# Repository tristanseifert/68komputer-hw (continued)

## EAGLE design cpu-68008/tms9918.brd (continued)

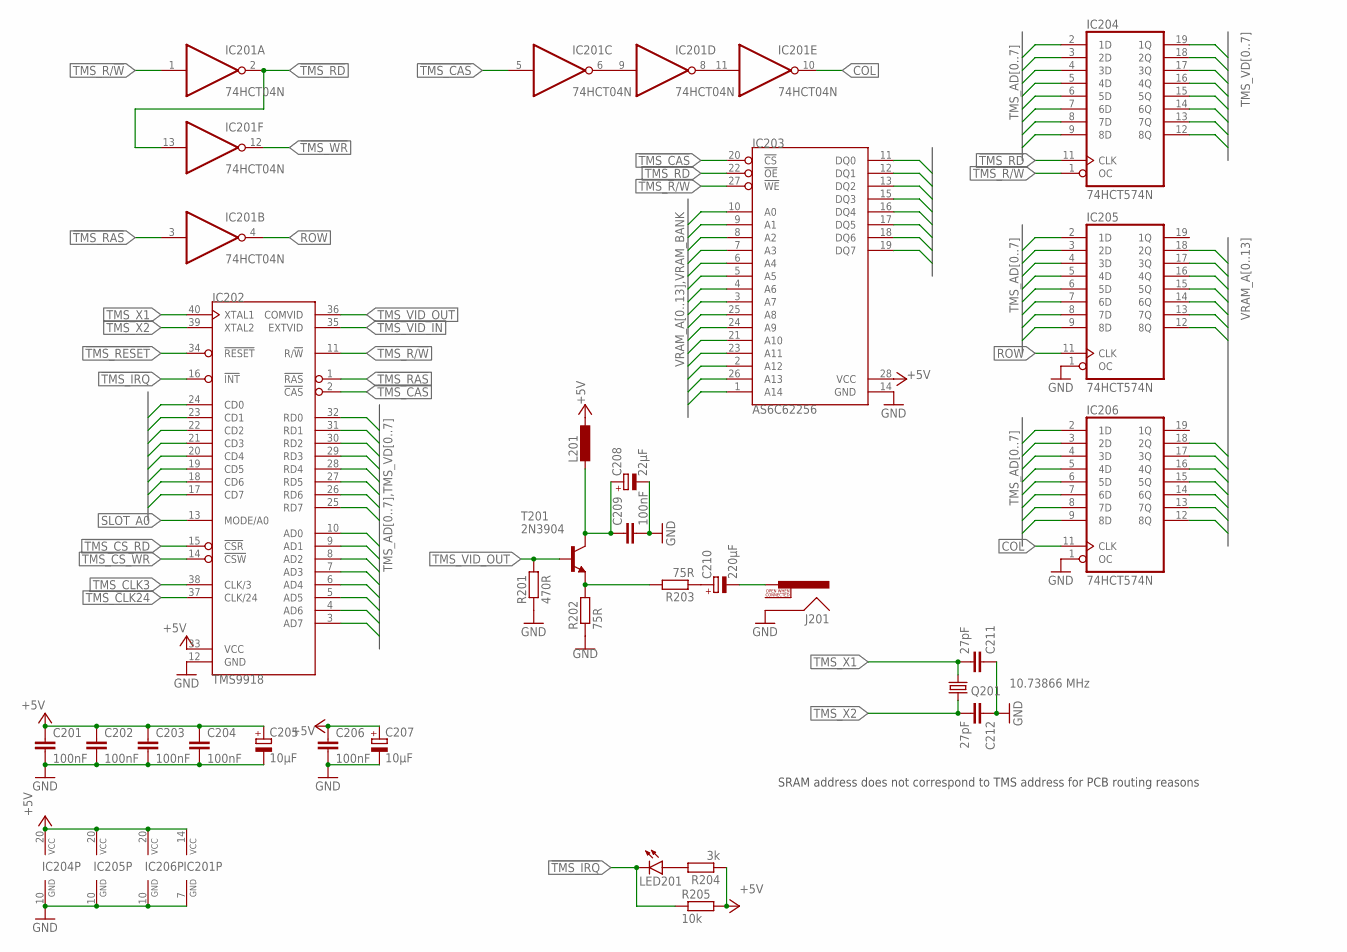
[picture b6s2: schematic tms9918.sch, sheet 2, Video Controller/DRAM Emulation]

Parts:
C201, C202, C203, C204, C206, C209: 100nF; C0805; MOUSER 710-885012207072
C205, C207: 10µF; SMC_B; MOUSER 581-TAJB106K020RNJV
C208: 22µF; E2-5; MOUSER 710-860010372002
C210: 220µF; E2,5-7; MOUSER 710-860020373010
C211, C212: 27pF; C0805; MOUSER 80-C0805C270K5HACTU
IC201: 74HCT04N; DIL14; MOUSER 595-SN74HCT04N
IC202: TMS9918; DIL40
IC203: AS6C62256; DIL28-6; MOUSER_SOCKET 575-1104762841001000
IC204, IC205, IC206: 74HCT574N; DIL20; MOUSER 595-SN74HCT574N
J201: RCALOCK; RCA_LOCK; MOUSER 502-PJRAN1X1U04AU
L201: L-EUL2012C; L2012C; MOUSER 963-BK2125HS101-T
LED201: LEDCHIPLED_1206; CHIPLED_1206; MOUSER 710-156120VS75300
Q201: 10.73866 MHz; HC49/S; MOUSER 449-LFXTAL029962REEL
R201: 470R; R2012; MOUSER 652-CR0805FX-4700ELF
R202, R203: 75R; R2012; MOUSER 652-CR0805FX-75R0ELF
R204: 3k; R2012; MOUSER 652-CR0805JW-302ELF
R205: 10k; R2012; MOUSER 652-CR0805FX-1002ELF
T201: 2N3904; TO92; MOUSER 512-2N3904BU

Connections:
!TMS_CAS: IC201.5 (I), IC202.2 (!CAS), IC203.20 (!CS)
!TMS_CS_RD: IC202.15 (!CSR); also elsewhere on the board
!TMS_CS_WR: IC202.14 (!CSW); also elsewhere on the board
!TMS_IRQ: IC202.16 (!INT), LED201.C, R205.1; also elsewhere on the board
!TMS_RAS: IC201.3 (I), IC202.1 (!RAS)
!TMS_RD: IC201.2 (O), IC201.13 (I), IC203.22 (!OE), IC204.11 (CLK)
!TMS_RESET: IC202.34 (!RESET); also elsewhere on the board
!TMS_WR: IC201.12 (O)
+5V: C201.1, C202.1, C203.1, C204.1, C205.+, C206.1, C207.+, IC201.14 (VCC), IC202.33 (VCC), IC203.28 (VCC), IC204.20 (VCC), IC205.20 (VCC), IC206.20 (VCC), L201.1, R204.1, R205.2; also elsewhere on the board
COL: IC201.10 (O), IC206.11 (CLK)
GND: C201.2, C202.2, C203.2, C204.2, C205.-, C206.2, C207.-, C208.-, C209.2, C211.1, C212.1, IC201.7 (GND), IC202.12 (GND), IC203.14 (GND), IC204.10 (GND), IC205.1 (OC), IC205.10 (GND), IC206.1 (OC), IC206.10 (GND), J201.SHELL, R201.1, R202.1; also elsewhere on the board
unnamed: IC201.8 (O), IC201.11 (I)
unnamed: IC201.6 (O), IC201.9 (I)
unnamed: C208.+, C209.1, L201.2, T201.1 (C)
unnamed: R202.2, R203.2, T201.3 (E)
unnamed: C210.+, R203.1
unnamed: C210.-, J201.PIN
unnamed: LED201.A, R204.2
ROW: IC201.4 (O), IC205.11 (CLK)
SLOT_A0: IC202.13 (MODE/A0); also elsewhere on the board
SLOT_D0: IC202.17 (CD7); also elsewhere on the board
SLOT_D1: IC202.18 (CD6); also elsewhere on the board
SLOT_D2: IC202.19 (CD5); also elsewhere on the board
SLOT_D3: IC202.20 (CD4); also elsewhere on the board
SLOT_D4: IC202.21 (CD3); also elsewhere on the board
SLOT_D5: IC202.22 (CD2); also elsewhere on the board
SLOT_D6: IC202.23 (CD1); also elsewhere on the board
SLOT_D7: IC202.24 (CD0); also elsewhere on the board
TMS_AD0: IC202.10 (AD0), IC204.2 (1D), IC205.9 (8D), IC206.9 (8D)
TMS_AD1: IC202.9 (AD1), IC204.3 (2D), IC205.8 (7D), IC206.8 (7D)
TMS_AD2: IC202.8 (AD2), IC204.4 (3D), IC205.7 (6D), IC206.7 (6D)
TMS_AD3: IC202.7 (AD3), IC204.5 (4D), IC205.6 (5D), IC206.6 (5D)
TMS_AD4: IC202.6 (AD4), IC204.6 (5D), IC205.5 (4D), IC206.5 (4D)
TMS_AD5: IC202.5 (AD5), IC204.7 (6D), IC205.4 (3D), IC206.4 (3D)
TMS_AD6: IC202.4 (AD6), IC204.8 (7D), IC205.3 (2D), IC206.3 (2D)
TMS_AD7: IC202.3 (AD7), IC204.9 (8D), IC205.2 (1D), IC206.2 (1D)
TMS_CLK3: IC202.38 (CLK/3); also elsewhere on the board
TMS_CLK24: IC202.37 (CLK/24)
TMS_R/!W!: IC201.1 (I), IC202.11 (R/!W!), IC203.27 (!WE), IC204.1 (OC)
TMS_VD0: IC202.32 (RD0), IC203.11 (DQ0), IC204.19 (1Q)
TMS_VD1: IC202.31 (RD1), IC203.12 (DQ1), IC204.18 (2Q)
TMS_VD2: IC202.30 (RD2), IC203.13 (DQ2), IC204.17 (3Q)
TMS_VD3: IC202.29 (RD3), IC203.15 (DQ3), IC204.16 (4Q)
TMS_VD4: IC202.28 (RD4), IC203.16 (DQ4), IC204.15 (5Q)
TMS_VD5: IC202.27 (RD5), IC203.17 (DQ5), IC204.14 (6Q)
TMS_VD6: IC202.26 (RD6), IC203.18 (DQ6), IC204.13 (7Q)
TMS_VD7: IC202.25 (RD7), IC203.19 (DQ7), IC204.12 (8Q)
TMS_VID_IN: IC202.35 (EXTVID)
TMS_VID_OUT: IC202.36 (COMVID), R201.2, T201.2 (B)
TMS_X1: C211.2, IC202.40 (XTAL1), Q201.1
TMS_X2: C212.2, IC202.39 (XTAL2), Q201.2
VRAM_A0: IC203.10 (A0), IC205.12 (8Q)
VRAM_A1: IC203.9 (A1), IC205.13 (7Q)
VRAM_A2: IC203.8 (A2), IC205.14 (6Q)
VRAM_A3: IC203.7 (A3), IC205.15 (5Q)
VRAM_A4: IC203.6 (A4), IC205.16 (4Q)
VRAM_A5: IC203.5 (A5), IC205.17 (3Q)
VRAM_A6: IC203.4 (A6), IC205.18 (2Q)
VRAM_A7: IC203.3 (A7), IC206.17 (3Q)
VRAM_A8: IC203.25 (A8), IC206.15 (5Q)
VRAM_A9: IC203.24 (A9), IC206.14 (6Q)
VRAM_A10: IC203.21 (A10), IC206.12 (8Q)
VRAM_A11: IC203.23 (A11), IC206.13 (7Q)
VRAM_A12: IC203.2 (A12), IC206.18 (2Q)
VRAM_A13: IC203.26 (A13), IC206.16 (4Q)
VRAM_BANK: IC203.1 (A14); also elsewhere on the board

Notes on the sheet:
SRAM address does not correspond to TMS address for PCB routing reasons

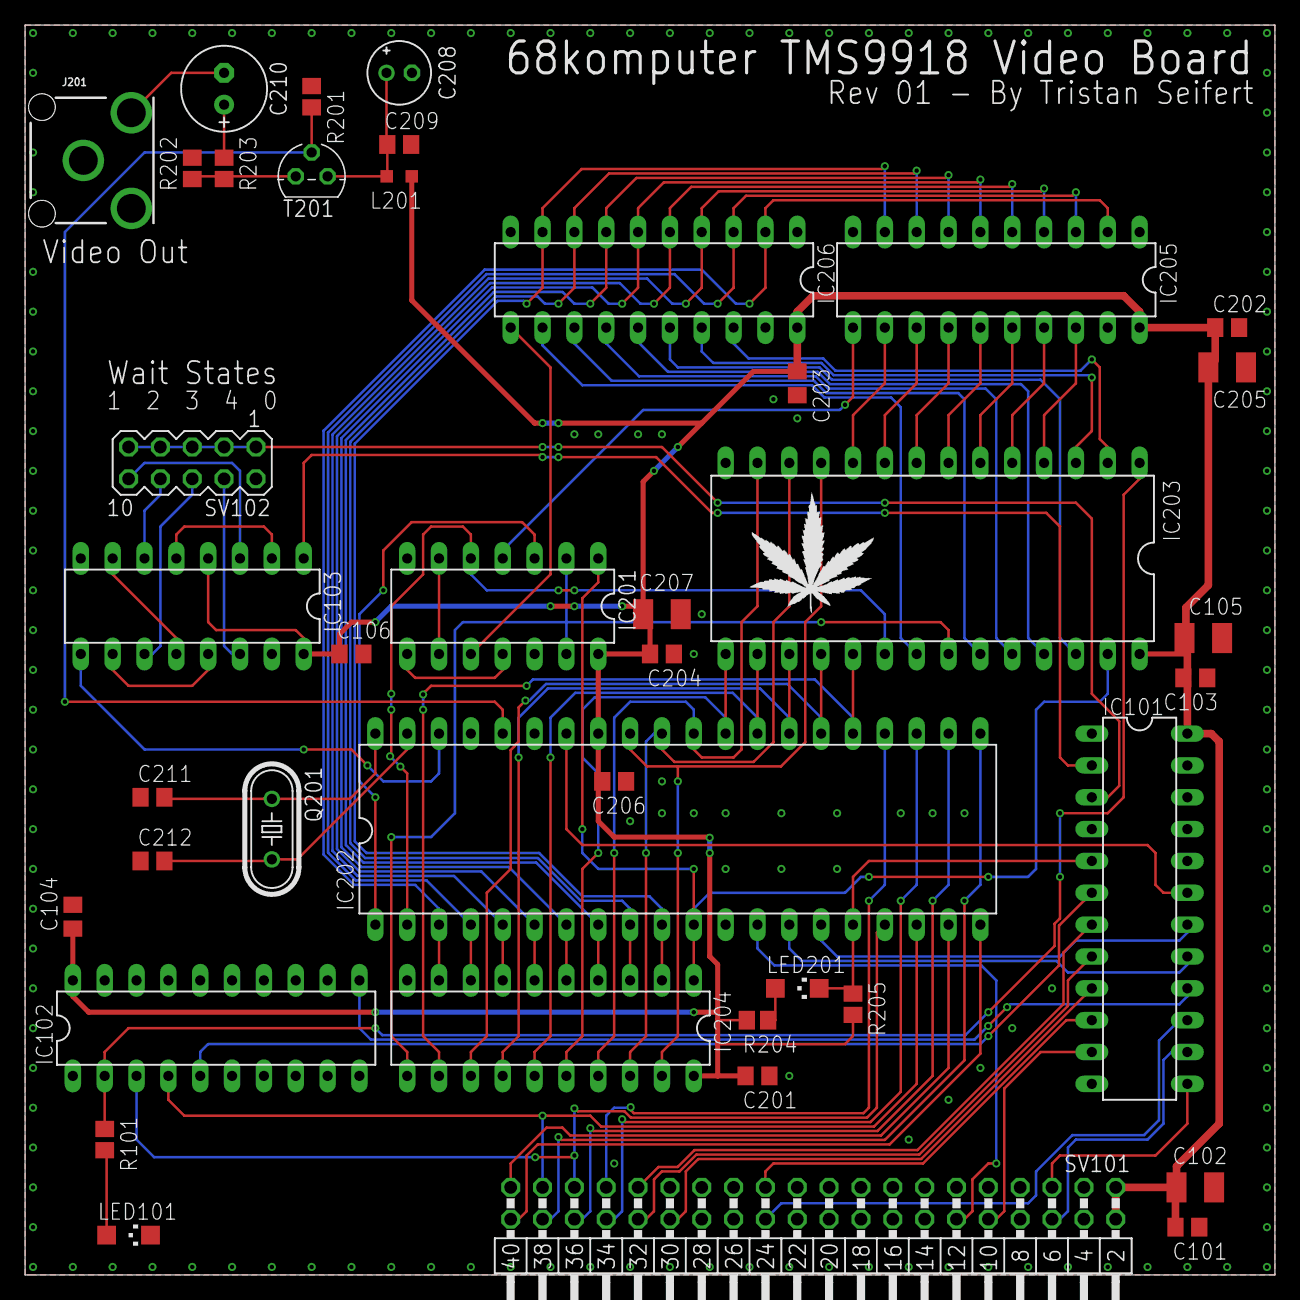
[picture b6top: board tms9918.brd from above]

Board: 2 copper layers, 99.7 x 99.7 mm, 42 parts (0 on the bottom side), 83 nets.

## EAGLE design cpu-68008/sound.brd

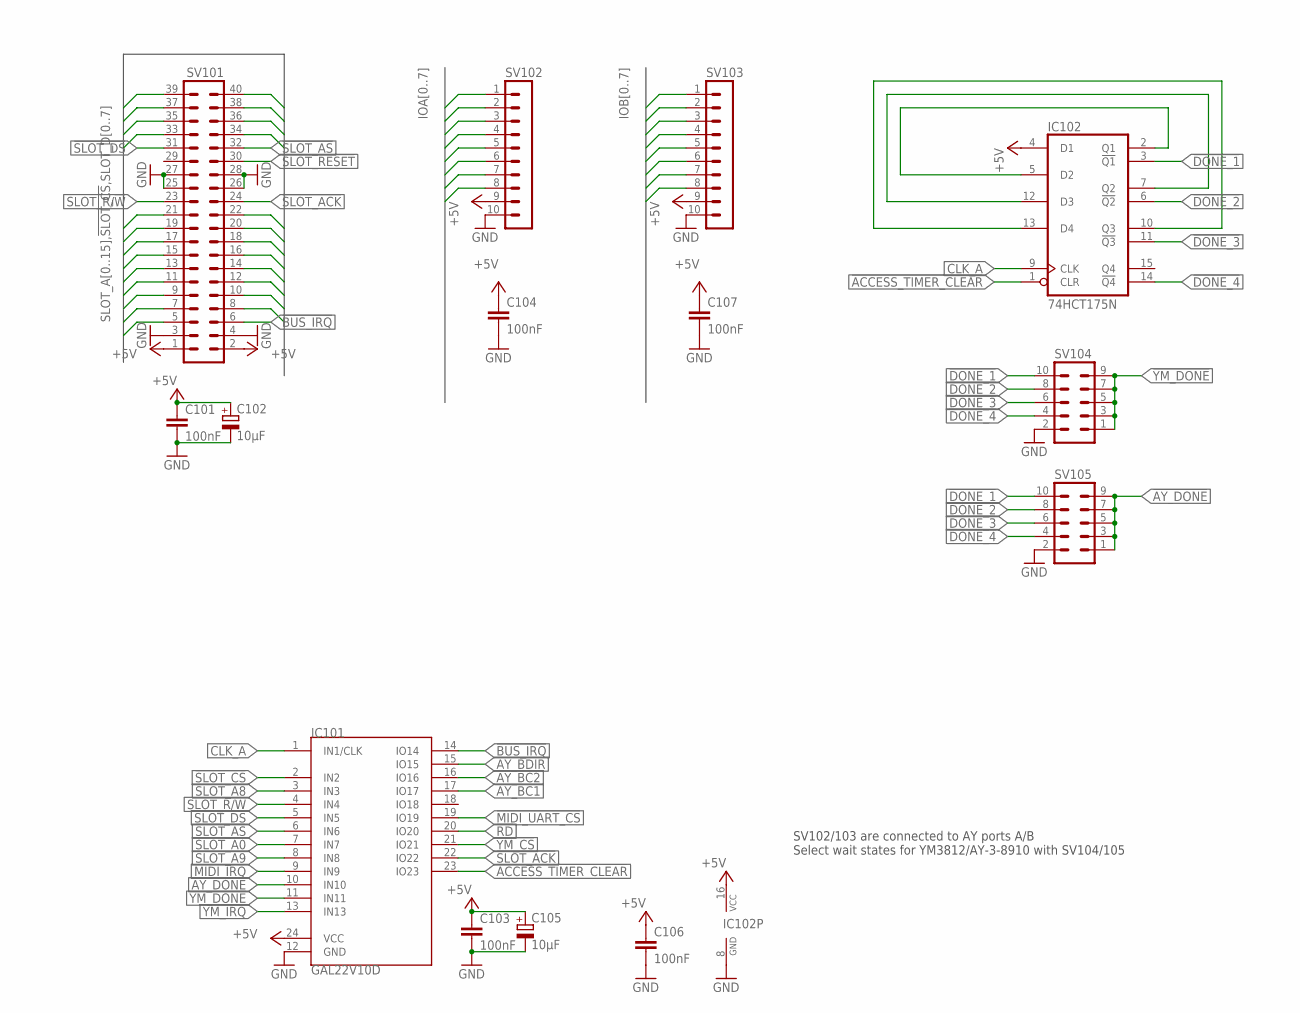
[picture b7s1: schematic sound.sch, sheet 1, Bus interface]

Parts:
C101, C103, C104, C106, C107: 100nF; C0805; MOUSER 710-885012207072
C102, C105: 10µF; SMC_B; MOUSER 581-TAJB106K020RNJV
IC101: GAL22V10D; DIL24S; MOUSER_SOCKET 575-11044324
IC102: 74HCT175N; DIL16; MOUSER 595-CD74HCT175E
SV101: MA20-2W
SV102, SV103: MA10-1
SV104, SV105: MA05-2

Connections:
!ACCESS_TIMER_CLEAR: IC101.23 (IO23), IC102.1 (CLR)
!AY_DONE: IC101.10 (IN10), SV105.1, SV105.3, SV105.5, SV105.7, SV105.9
!BUS_IRQ: IC101.14 (IO14), SV101.6
!DONE_1: IC102.3 (!Q1), SV104.10, SV105.10
!DONE_2: IC102.6 (!Q2), SV104.8, SV105.8
!DONE_3: IC102.11 (!Q3), SV104.6, SV105.6
!DONE_4: IC102.14 (!Q4), SV104.4, SV105.4
!MIDI_IRQ: IC101.9 (IN9); also elsewhere on the board
!MIDI_UART_CS: IC101.19 (IO19); also elsewhere on the board
!RD: IC101.20 (IO20); also elsewhere on the board
!SLOT_ACK: IC101.22 (IO22), SV101.24
!SLOT_AS: IC101.6 (IN6), SV101.32
!SLOT_CS: IC101.2 (IN2), SV101.5
!SLOT_DS: IC101.5 (IN5), SV101.31
!SLOT_RESET: SV101.30; also elsewhere on the board
!YM_CS: IC101.21 (IO21); also elsewhere on the board
!YM_DONE: IC101.11 (IN11), SV104.1, SV104.3, SV104.5, SV104.7, SV104.9
!YM_IRQ: IC101.13 (IN13); also elsewhere on the board
+5V: C101.1, C102.+, C103.1, C104.1, C105.+, C106.1, C107.1, IC101.24 (VCC), IC102.4 (D1), IC102.16 (VCC), SV101.1, SV101.2, SV102.9, SV103.9; also elsewhere on the board
AY_BC1: IC101.17 (IO17); also elsewhere on the board
AY_BC2: IC101.16 (IO16); also elsewhere on the board
AY_BDIR: IC101.15 (IO15); also elsewhere on the board
CLK_A: IC101.1 (IN1/CLK), IC102.9 (CLK); also elsewhere on the board
GND: C101.2, C102.-, C103.2, C104.2, C105.-, C106.2, C107.2, IC101.12 (GND), IC102.8 (GND), SV101.3, SV101.4, SV101.25, SV101.26, SV101.27, SV101.28, SV102.10, SV103.10, SV104.2, SV105.2; also elsewhere on the board
IOA0: SV102.1; also elsewhere on the board
IOA1: SV102.2; also elsewhere on the board
IOA2: SV102.3; also elsewhere on the board
IOA3: SV102.4; also elsewhere on the board
IOA4: SV102.5; also elsewhere on the board
IOA5: SV102.6; also elsewhere on the board
IOA6: SV102.7; also elsewhere on the board
IOA7: SV102.8; also elsewhere on the board
IOB0: SV103.1; also elsewhere on the board
IOB1: SV103.2; also elsewhere on the board
IOB2: SV103.3; also elsewhere on the board
IOB3: SV103.4; also elsewhere on the board
IOB4: SV103.5; also elsewhere on the board
IOB5: SV103.6; also elsewhere on the board
IOB6: SV103.7; also elsewhere on the board
IOB7: SV103.8; also elsewhere on the board
unnamed: IC102.10 (Q3), IC102.13 (D4)
unnamed: IC102.2 (Q1), IC102.5 (D2)
unnamed: IC102.7 (Q2), IC102.12 (D3)
SLOT_A0: IC101.7 (IN7), SV101.12; also elsewhere on the board
SLOT_A1: SV101.10; also elsewhere on the board
SLOT_A2: SV101.8; also elsewhere on the board
SLOT_A3: SV101.7
SLOT_A4: SV101.9
SLOT_A5: SV101.11
SLOT_A6: SV101.14
SLOT_A7: SV101.13
SLOT_A8: IC101.3 (IN3), SV101.16
SLOT_A9: IC101.8 (IN8), SV101.15
SLOT_A10: SV101.18
SLOT_A11: SV101.17
SLOT_A12: SV101.20
SLOT_A13: SV101.19
SLOT_A14: SV101.22
SLOT_A15: SV101.21
SLOT_D0: SV101.35; also elsewhere on the board
SLOT_D1: SV101.37; also elsewhere on the board
SLOT_D2: SV101.39; also elsewhere on the board
SLOT_D3: SV101.40; also elsewhere on the board
SLOT_D4: SV101.38; also elsewhere on the board
SLOT_D5: SV101.36; also elsewhere on the board
SLOT_D6: SV101.34; also elsewhere on the board
SLOT_D7: SV101.33; also elsewhere on the board
SLOT_R/!W!: IC101.4 (IN4), SV101.23; also elsewhere on the board

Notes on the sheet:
SV102/103 are connected to AY ports A/B Select wait states for YM3812/AY-3-8910 with SV104/105

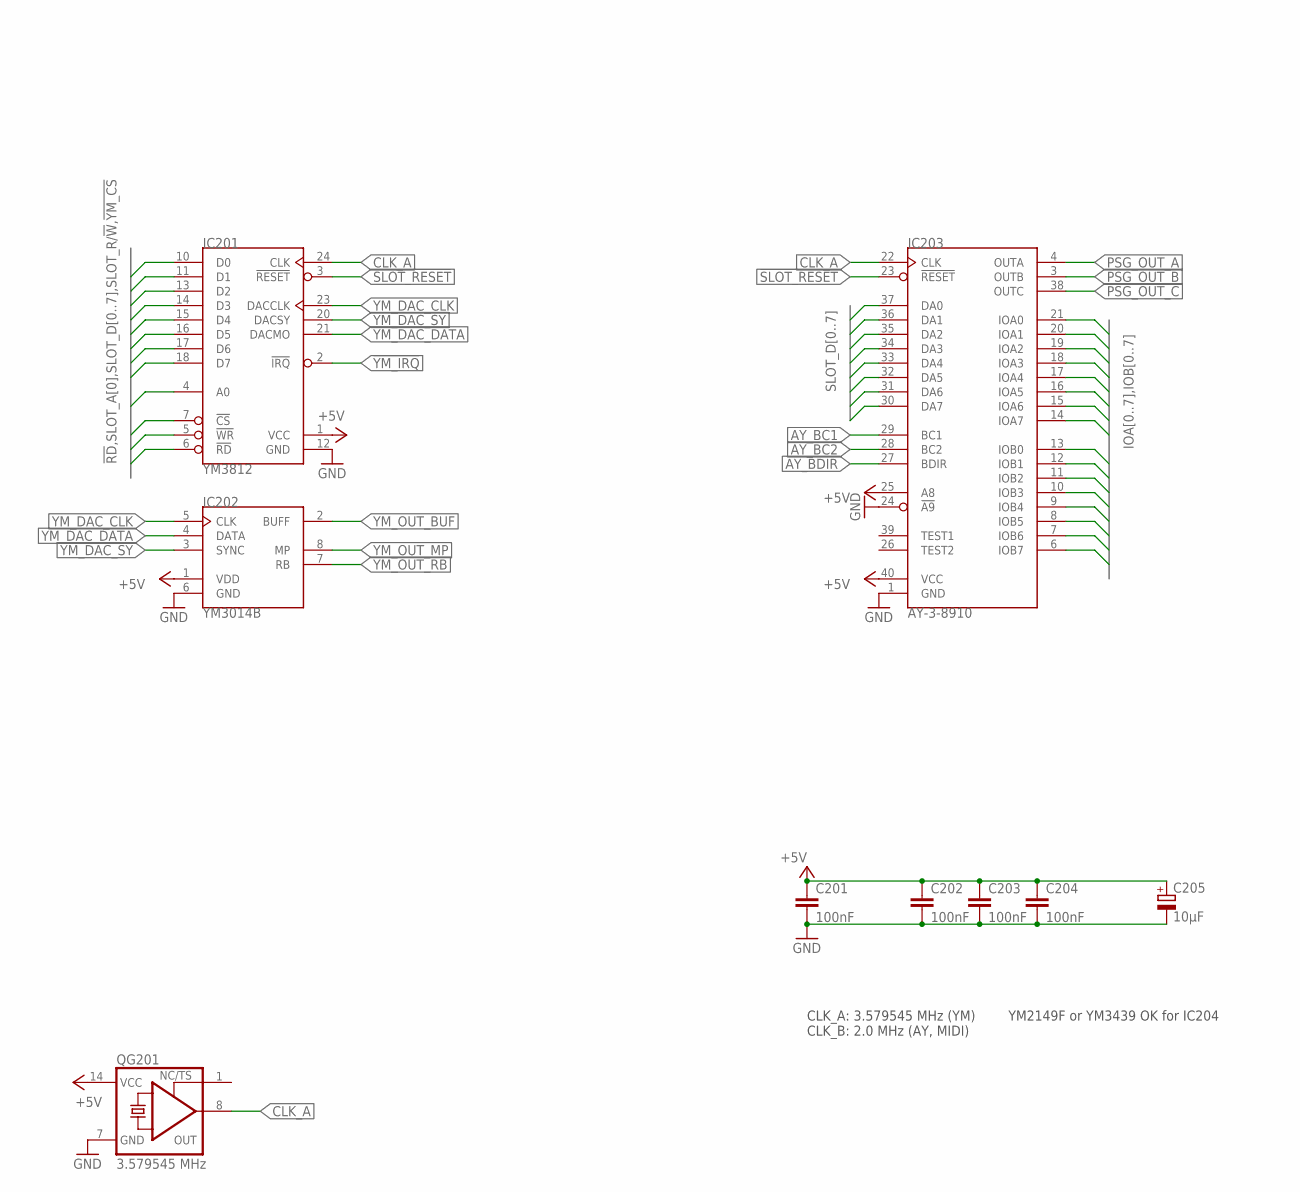
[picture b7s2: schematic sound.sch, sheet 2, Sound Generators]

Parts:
C201, C202, C203, C204: 100nF; C0805; MOUSER 710-885012207072
C205: 10µF; SMC_B; MOUSER 581-TAJB106K020RNJV
IC201: YM3812; DIL24; MOUSER_SOCKET 575-1104762441001000
IC202: YM3014B; DIL8; MOUSER_SOCKET 575-1104730841001000
IC203: AY-3-8910; DIL40; MOUSER_SOCKET 575-11044640
QG201: 3.579545 MHz; DIL14S; MOUSER 520-TCF357-X

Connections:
!RD: IC201.6 (!RD); also elsewhere on the board
!SLOT_RESET: IC201.3 (!RESET), IC203.23 (!RESET); also elsewhere on the board
!YM_CS: IC201.7 (!CS); also elsewhere on the board
!YM_IRQ: IC201.2 (!IRQ); also elsewhere on the board
+5V: C201.1, C202.1, C203.1, C204.1, C205.+, IC201.1 (VCC), IC202.1 (VDD), IC203.25 (A8), IC203.40 (VCC), QG201.14 (VCC); also elsewhere on the board
AY_BC1: IC203.29 (BC1); also elsewhere on the board
AY_BC2: IC203.28 (BC2); also elsewhere on the board
AY_BDIR: IC203.27 (BDIR); also elsewhere on the board
CLK_A: IC201.24 (CLK), IC203.22 (CLK), QG201.8 (OUT); also elsewhere on the board
GND: C201.2, C202.2, C203.2, C204.2, C205.-, IC201.12 (GND), IC202.6 (GND), IC203.1 (GND), IC203.24 (!A9), QG201.7 (GND); also elsewhere on the board
IOA0: IC203.21 (IOA0); also elsewhere on the board
IOA1: IC203.20 (IOA1); also elsewhere on the board
IOA2: IC203.19 (IOA2); also elsewhere on the board
IOA3: IC203.18 (IOA3); also elsewhere on the board
IOA4: IC203.17 (IOA4); also elsewhere on the board
IOA5: IC203.16 (IOA5); also elsewhere on the board
IOA6: IC203.15 (IOA6); also elsewhere on the board
IOA7: IC203.14 (IOA7); also elsewhere on the board
IOB0: IC203.13 (IOB0); also elsewhere on the board
IOB1: IC203.12 (IOB1); also elsewhere on the board
IOB2: IC203.11 (IOB2); also elsewhere on the board
IOB3: IC203.10 (IOB3); also elsewhere on the board
IOB4: IC203.9 (IOB4); also elsewhere on the board
IOB5: IC203.8 (IOB5); also elsewhere on the board
IOB6: IC203.7 (IOB6); also elsewhere on the board
IOB7: IC203.6 (IOB7); also elsewhere on the board
PSG_OUT_A: IC203.4 (OUTA); also elsewhere on the board
PSG_OUT_B: IC203.3 (OUTB); also elsewhere on the board
PSG_OUT_C: IC203.38 (OUTC); also elsewhere on the board
SLOT_A0: IC201.4 (A0); also elsewhere on the board
SLOT_D0: IC201.10 (D0), IC203.37 (DA0); also elsewhere on the board
SLOT_D1: IC201.11 (D1), IC203.36 (DA1); also elsewhere on the board
SLOT_D2: IC201.13 (D2), IC203.35 (DA2); also elsewhere on the board
SLOT_D3: IC201.14 (D3), IC203.34 (DA3); also elsewhere on the board
SLOT_D4: IC201.15 (D4), IC203.33 (DA4); also elsewhere on the board
SLOT_D5: IC201.16 (D5), IC203.32 (DA5); also elsewhere on the board
SLOT_D6: IC201.17 (D6), IC203.31 (DA6); also elsewhere on the board
SLOT_D7: IC201.18 (D7), IC203.30 (DA7); also elsewhere on the board
SLOT_R/!W!: IC201.5 (!WR); also elsewhere on the board
YM_DAC_CLK: IC201.23 (DACCLK), IC202.5 (CLK)
YM_DAC_DATA: IC201.21 (DACMO), IC202.4 (DATA)
YM_DAC_SY: IC201.20 (DACSY), IC202.3 (SYNC)
YM_OUT_BUF: IC202.2 (BUFF); also elsewhere on the board
YM_OUT_MP: IC202.8 (MP); also elsewhere on the board
YM_OUT_RB: IC202.7 (RB); also elsewhere on the board

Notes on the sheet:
CLK_A: 3.579545 MHz (YM) CLK_B: 2.0 MHz (AY, MIDI)
YM2149F or YM3439 OK for IC204

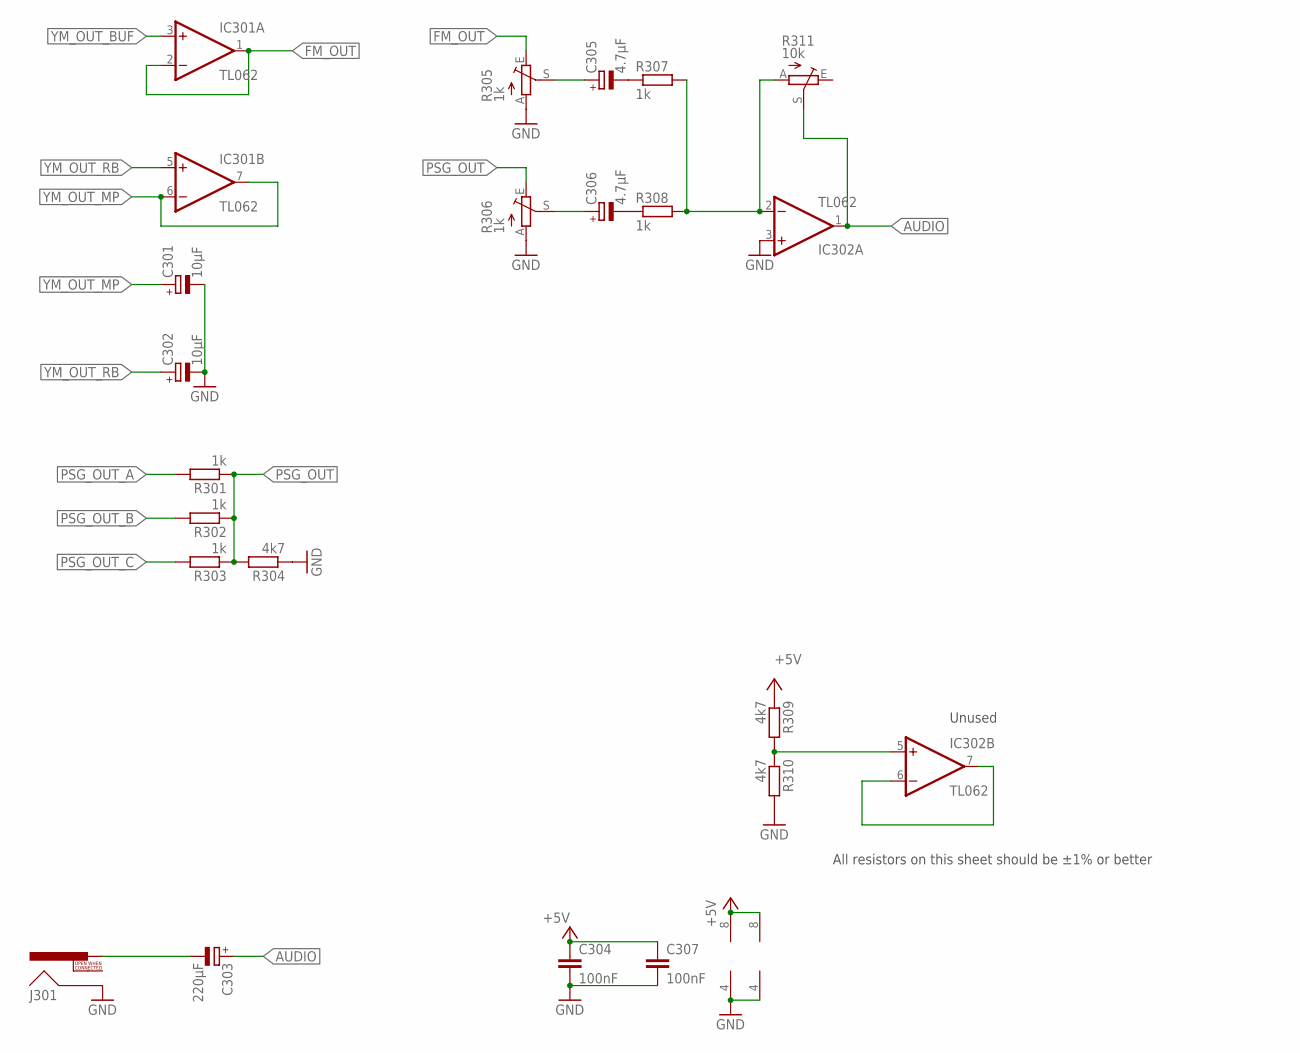
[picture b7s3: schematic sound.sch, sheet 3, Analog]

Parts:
C301, C302: 10µF; E2-5; MOUSER 710-860020472003
C303: 220µF; E2,5-6; MOUSER 710-860020373010
C304, C307: 100nF; C0805; MOUSER 710-885012207072
C305, C306: 4.7µF; E2-5; MOUSER 710-860020472001
IC301, IC302: TL062; DIL08; MOUSER 595-TL062CP
J301: RCALOCK; RCA_LOCK; MOUSER 502-PJRAN1X1U03AUX
R301, R302, R303, R307, R308: 1k; R2012; MOUSER 652-CR0805FX-1001ELF
R304, R309, R310: 4k7; R2012; MOUSER 652-CR0805FX-4701ELF
R305, R306: 1k; PT-10S; MOUSER PT10LH01-102A2020-S
R311: 10k; PT-10S; MOUSER 531-PT10H-10K-S

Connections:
+5V: C304.1, C307.1, IC301.8 (V+), IC302.8 (V+), R309.1; also elsewhere on the board
AUDIO: C303.+, IC302.1 (OUT), R311.S
FM_OUT: IC301.1 (OUT), IC301.2 (-IN), R305.E
GND: C301.-, C302.-, C304.2, C307.2, IC301.4 (V-), IC302.3 (+IN), IC302.4 (V-), J301.SHELL, R304.1, R305.A, R306.A, R310.2; also elsewhere on the board
unnamed: C305.+, R305.S
unnamed: C303.-, J301.PIN
unnamed: C306.+, R306.S
unnamed: C305.-, R307.1
unnamed: C306.-, R308.1
unnamed: IC302.2 (-IN), R307.2, R308.2, R311.A
unnamed: IC302.6 (-IN), IC302.7 (OUT)
unnamed: IC302.5 (+IN), R309.2, R310.1
PSG_OUT: R301.1, R302.1, R303.1, R304.2, R306.E
PSG_OUT_A: R301.2; also elsewhere on the board
PSG_OUT_B: R302.2; also elsewhere on the board
PSG_OUT_C: R303.2; also elsewhere on the board
YM_OUT_BUF: IC301.3 (+IN); also elsewhere on the board
YM_OUT_MP: C301.+, IC301.6 (-IN), IC301.7 (OUT); also elsewhere on the board
YM_OUT_RB: C302.+, IC301.5 (+IN); also elsewhere on the board

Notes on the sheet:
All resistors on this sheet should be ±1% or better
Unused

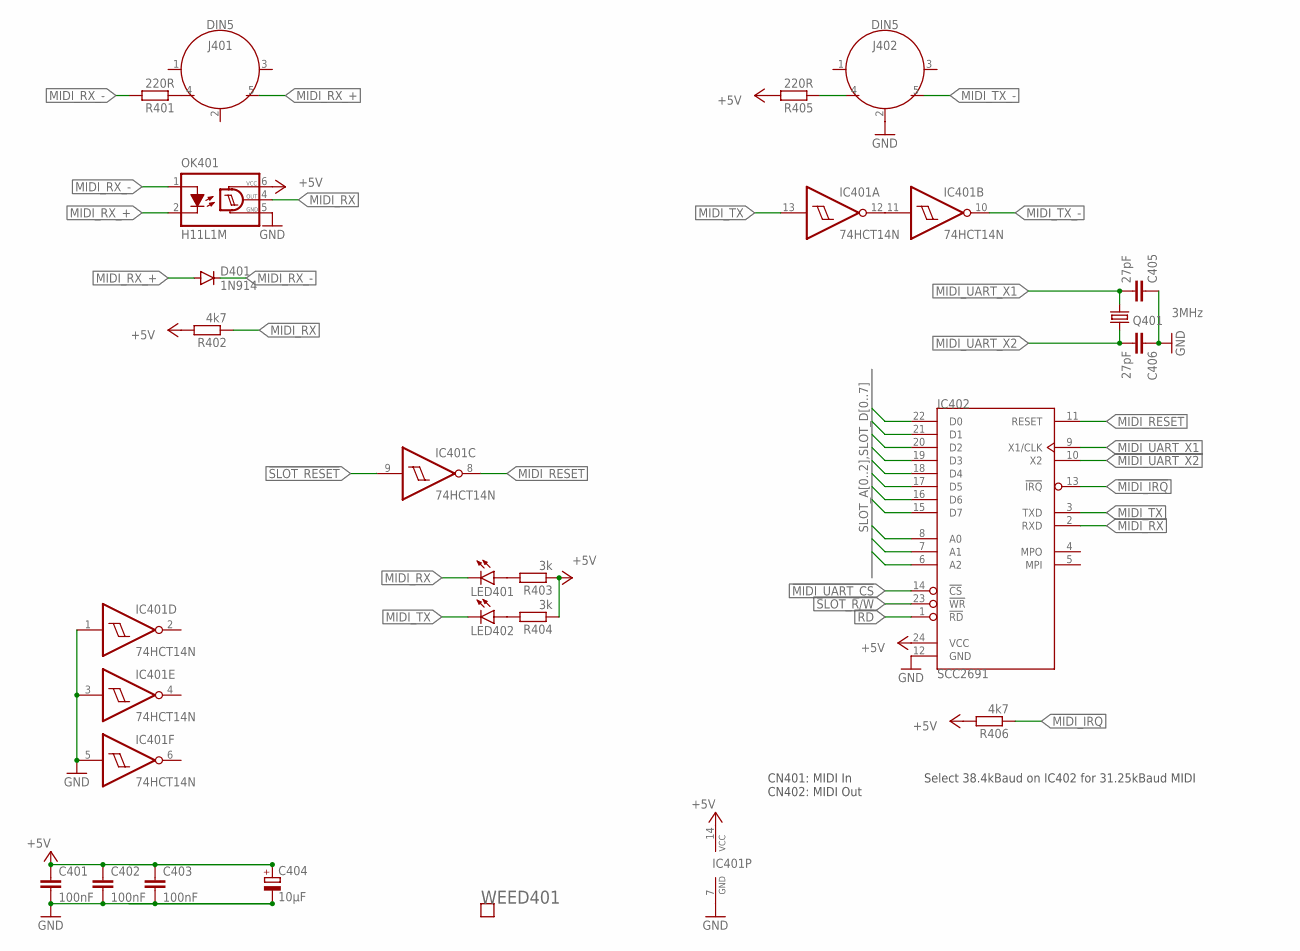
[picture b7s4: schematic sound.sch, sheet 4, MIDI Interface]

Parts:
C401, C402, C403: 100nF; C0805; MOUSER 710-885012207072
C404: 10µF; SMC_B; MOUSER 581-TAJB106K020RNJV
C405, C406: 27pF; C0805; MOUSER 80-C0805C270K5HACTU
D401: 1N914; DO35-10; MOUSER 512-1N914TR
IC401: 74HCT14N; DIL14; MOUSER 595-SN74HCT14N
IC402: SCC2691; DIL24S; MOUSER_SOCKET 575-11044324
J401, J402: DIN5; DIN5-RA-PTH
LED401, LED402: LEDCHIPLED_1206; CHIPLED_1206; MOUSER 710-156120VS75300
OK401: H11L1M; DIL06; MOUSER 512-H11L1M
Q401: 3MHz; HC49/S; MOUSER 520-HCA300-SX
R401, R405: 220R; R2012; MOUSER 652-CR0805FX-2200ELF
R402, R406: 4k7; R2012; MOUSER 652-CR0805FX-4701ELF
R403, R404: 3k; R2012; MOUSER 652-CR0805JW-302ELF
WEED401: WEED; DOINK

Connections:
!MIDI_IRQ: IC402.13 (!IRQ), R406.1; also elsewhere on the board
!MIDI_UART_CS: IC402.14 (!CS); also elsewhere on the board
!RD: IC402.1 (!RD); also elsewhere on the board
!SLOT_RESET: IC401.9 (I); also elsewhere on the board
+5V: C401.1, C402.1, C403.1, C404.+, IC401.14 (VCC), IC402.24 (VCC), OK401.6 (VCC), R402.2, R403.1, R404.1, R405.2, R406.2; also elsewhere on the board
GND: C401.2, C402.2, C403.2, C404.-, C405.1, C406.1, IC401.1 (I), IC401.3 (I), IC401.5 (I), IC401.7 (GND), IC402.12 (GND), J402.2, OK401.5 (GND); also elsewhere on the board
MIDI_RESET: IC401.8 (O), IC402.11 (RESET)
MIDI_RX: IC402.2 (RXD), LED401.C, OK401.4 (OUT), R402.1
MIDI_RX_+: D401.A, J401.5, OK401.2 (C)
MIDI_RX_-: D401.C, OK401.1 (A), R401.2
MIDI_TX: IC401.13 (I), IC402.3 (TXD), LED402.C
MIDI_TX_-: IC401.10 (O), J402.5
MIDI_UART_X1: C405.2, IC402.9 (X1/CLK), Q401.1
MIDI_UART_X2: C406.2, IC402.10 (X2), Q401.2
unnamed: LED401.A, R403.2
unnamed: LED402.A, R404.2
unnamed: J401.4, R401.1
unnamed: IC401.11 (I), IC401.12 (O)
unnamed: J402.4, R405.1
SLOT_A0: IC402.8 (A0); also elsewhere on the board
SLOT_A1: IC402.7 (A1); also elsewhere on the board
SLOT_A2: IC402.6 (A2); also elsewhere on the board
SLOT_D0: IC402.22 (D0); also elsewhere on the board
SLOT_D1: IC402.21 (D1); also elsewhere on the board
SLOT_D2: IC402.20 (D2); also elsewhere on the board
SLOT_D3: IC402.19 (D3); also elsewhere on the board
SLOT_D4: IC402.18 (D4); also elsewhere on the board
SLOT_D5: IC402.17 (D5); also elsewhere on the board
SLOT_D6: IC402.16 (D6); also elsewhere on the board
SLOT_D7: IC402.15 (D7); also elsewhere on the board
SLOT_R/!W!: IC402.23 (!WR); also elsewhere on the board

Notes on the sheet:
CN401: MIDI In CN402: MIDI Out
Select 38.4kBaud on IC402 for 31.25kBaud MIDI

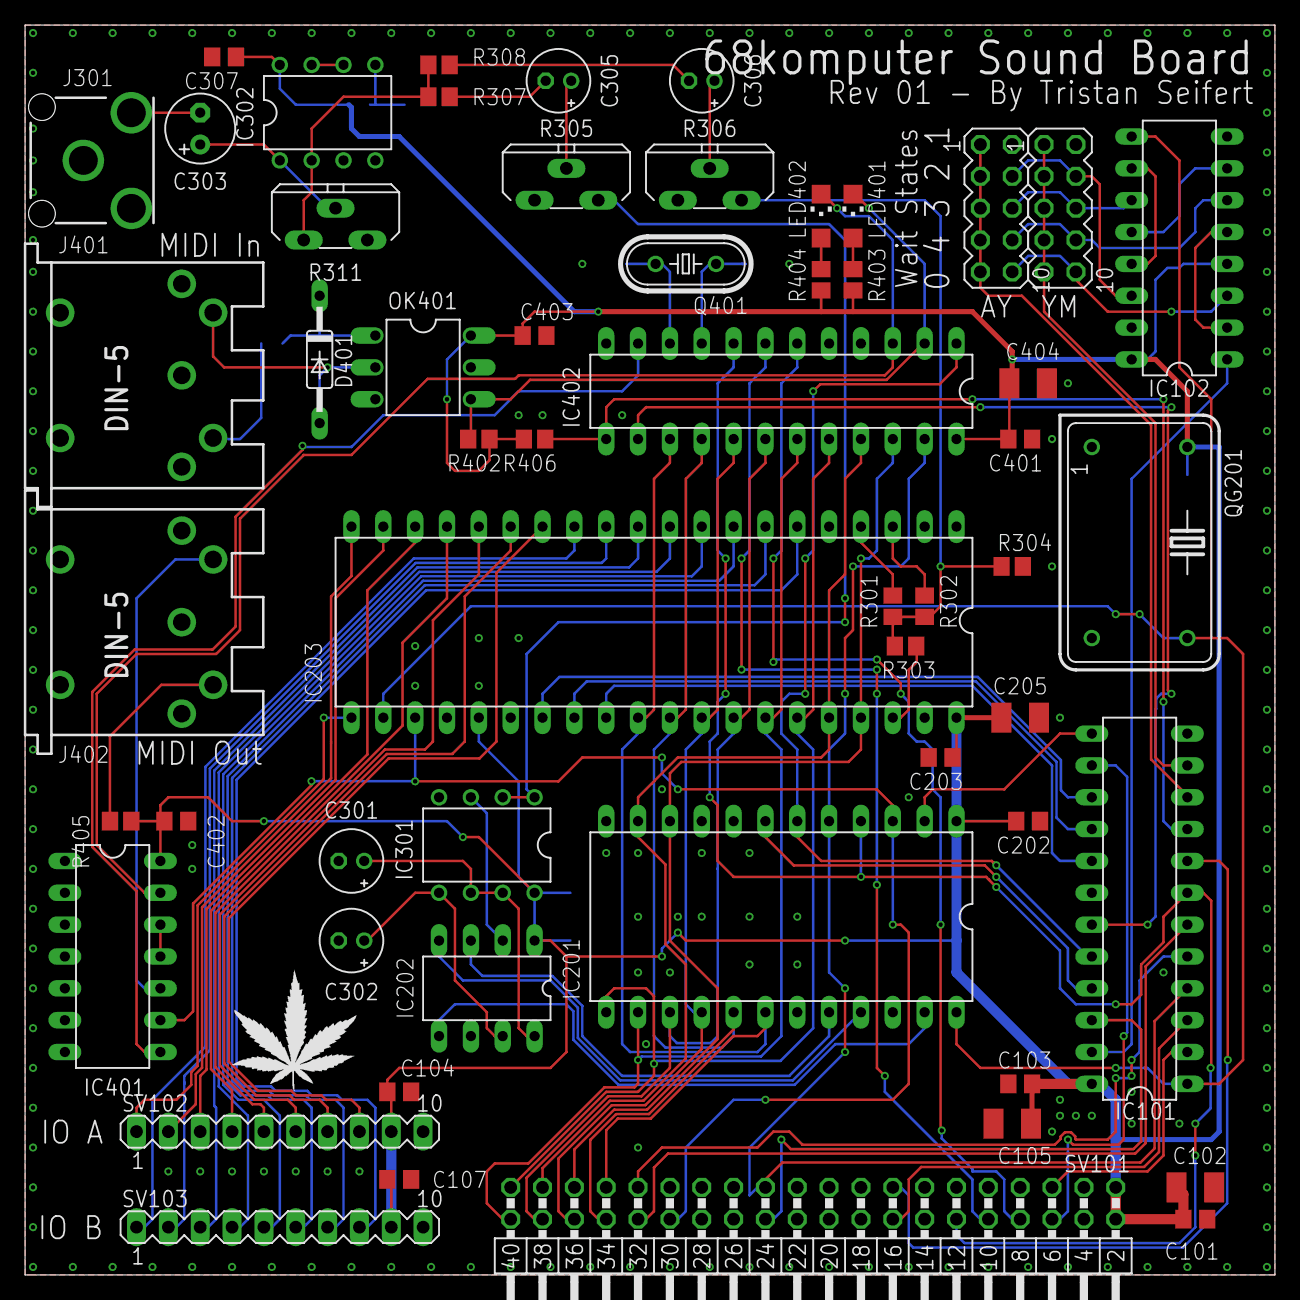
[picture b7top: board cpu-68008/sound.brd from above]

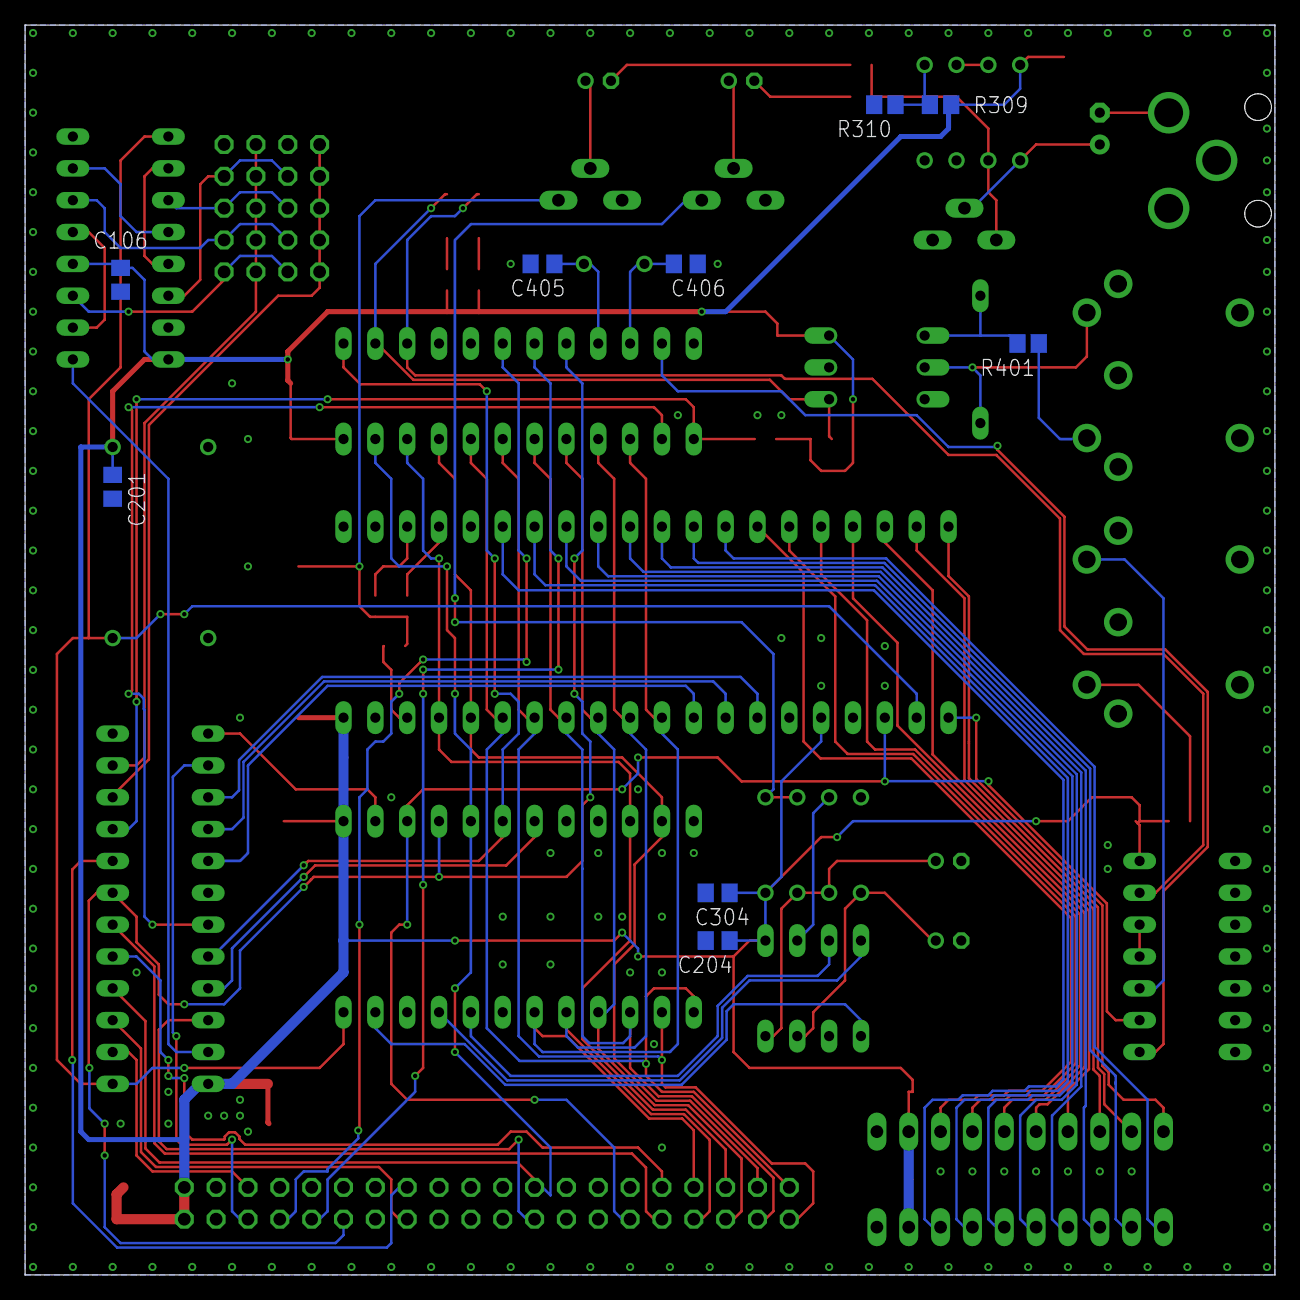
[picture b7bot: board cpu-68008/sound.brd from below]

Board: 2 copper layers, 99.7 x 99.7 mm, 66 parts (9 on the bottom side), 90 nets.
